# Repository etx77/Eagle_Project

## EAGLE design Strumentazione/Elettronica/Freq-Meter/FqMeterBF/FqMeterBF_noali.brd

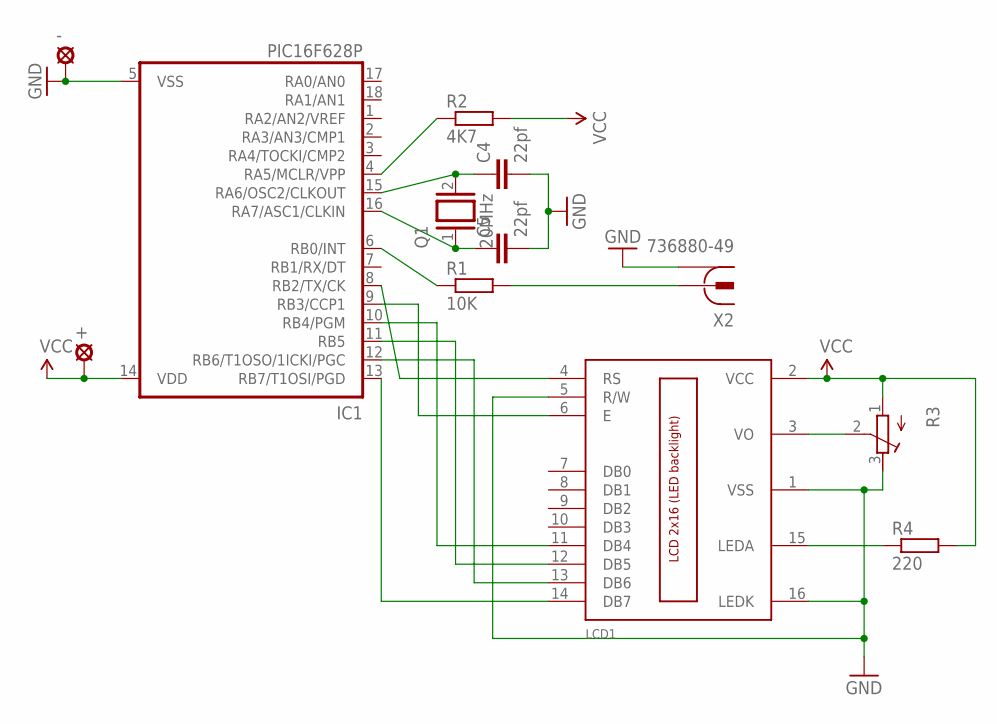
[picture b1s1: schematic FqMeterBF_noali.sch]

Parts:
+: LSP10
-: LSP10
C4, C5: 22pf; C025-024X044
IC1: PIC16F628P; DIL18
LCD1: LCD_2X16; HY-1602F
Q1: 20MHz; QS
R1: 10K; 0207/12
R2: 4K7; 0207/12
R3: R-TRIMM3339P; RTRIM3339P
R4: 220; 0207/12
X2: 736880-49

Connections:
GND: -.MP, C4.2, C5.2, IC1.5 (VSS), LCD1.1 (VSS), LCD1.5 (R/W), LCD1.16 (LEDK), R3.3 (E), X2.1, X2.1@1 (1), X2.1@2 (1)
unnamed: LCD1.15 (LEDA), R4.1
unnamed: C4.1, IC1.15 (RA6/OSC2/CLKOUT), Q1.2
unnamed: C5.1, IC1.16 (RA7/ASC1/CLKIN), Q1.1
unnamed: IC1.6 (RB0/INT), R1.1
unnamed: IC1.4 (RA5/MCLR/VPP), R2.1
unnamed: IC1.8 (RB2/TX/CK), LCD1.4 (RS)
unnamed: IC1.9 (RB3/CCP1), LCD1.6 (E)
unnamed: R1.2, X2.2
unnamed: LCD1.3 (VO), R3.2 (S)
unnamed: IC1.10 (RB4/PGM), LCD1.11 (DB4)
unnamed: IC1.11 (RB5), LCD1.12 (DB5)
unnamed: IC1.12 (RB6/T1OSO/1ICKI/PGC), LCD1.13 (DB6)
unnamed: IC1.13 (RB7/T1OSI/PGD), LCD1.14 (DB7)
unnamed: +.MP, IC1.14 (VDD), LCD1.2 (VCC), R2.2, R3.1 (A), R4.2

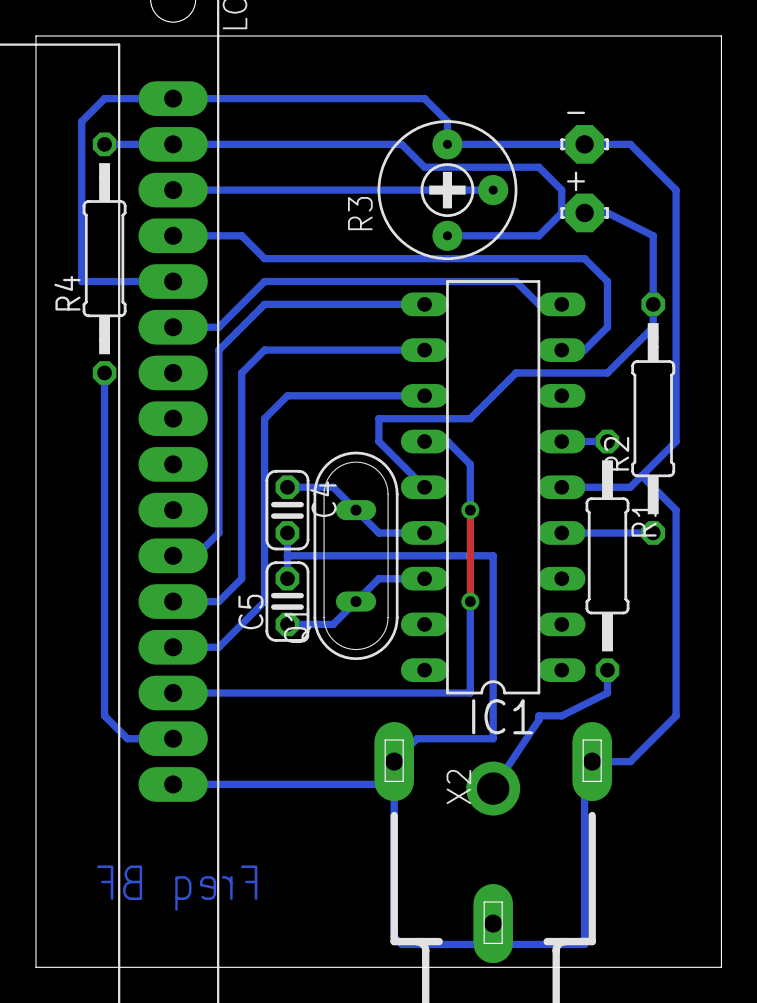
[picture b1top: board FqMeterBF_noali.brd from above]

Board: 2 copper layers, 38.1 x 51.7 mm, 12 parts (0 on the bottom side), 15 nets.

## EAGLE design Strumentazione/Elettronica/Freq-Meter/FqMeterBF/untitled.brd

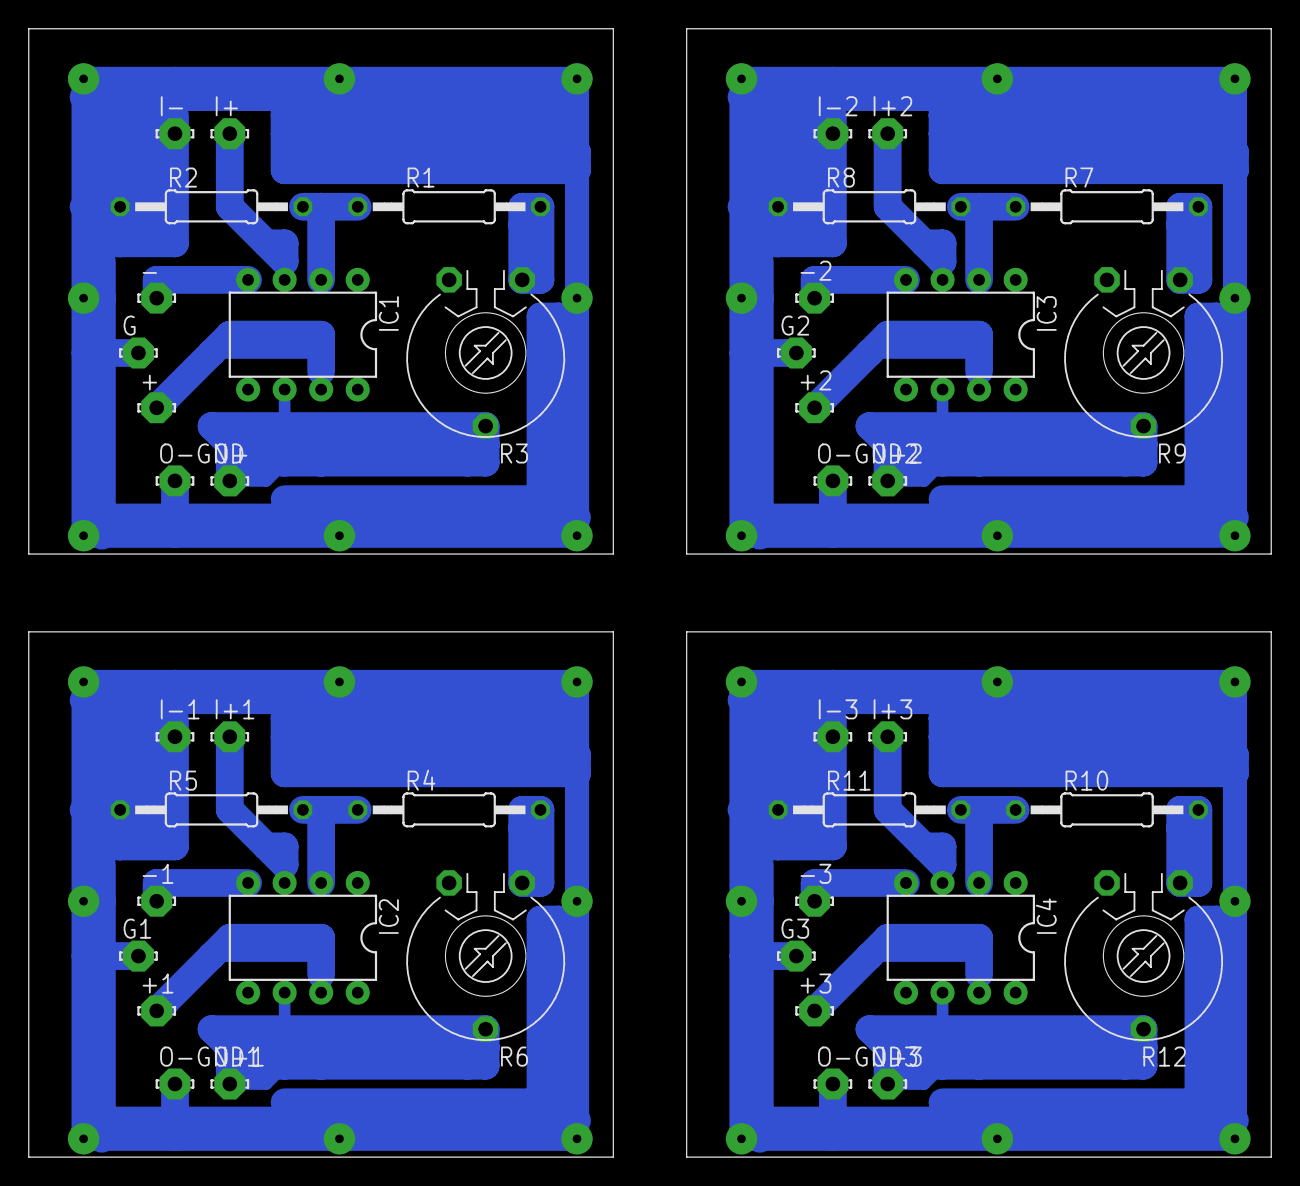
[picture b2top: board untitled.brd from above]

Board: 2 copper layers, 86.3 x 78.4 mm, 44 parts (0 on the bottom side), 28 nets.

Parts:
+, +1, +2, +3: LSP10
-, -1, -2, -3: LSP10
G, G1, G2, G3: LSP10
I+, I+1, I+2, I+3: LSP10
I-, I-1, I-2, I-3: LSP10
IC1, IC2, IC3, IC4: LM741P; DIL08
O+, O+1, O+2, O+3: LSP10
O-GND, O-GND1, O-GND2, O-GND3: LSP10
R1, R4, R7, R10: 68K; 0207/12
R2, R5, R8, R11: 1K2; 0207/12
R3, R6, R9, R12: 47K; PT-10

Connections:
+12V: +.MP, IC1.7
+12V1: +1.MP, IC2.7
+12V2: +2.MP, IC3.7
+12V3: +3.MP, IC4.7
-12V: -.MP, IC1.4
-12V1: -1.MP, IC2.4
-12V2: -2.MP, IC3.4
-12V3: -3.MP, IC4.4
unnamed: IC1.2, R1.1, R2.2
unnamed: R1.2, R3.1
unnamed: IC1.6, O+.MP, R3.3
unnamed: I+.MP, IC1.3
unnamed: G.MP, I-.MP, O-GND.MP, R2.1
unnamed: IC2.2, R4.1, R5.2
unnamed: R4.2, R6.1
unnamed: IC2.6, O+1.MP, R6.3
unnamed: I+1.MP, IC2.3
unnamed: G1.MP, I-1.MP, O-GND1.MP, R5.1
unnamed: IC3.2, R7.1, R8.2
unnamed: R7.2, R9.1
unnamed: IC3.6, O+2.MP, R9.3
unnamed: I+2.MP, IC3.3
unnamed: G2.MP, I-2.MP, O-GND2.MP, R8.1
unnamed: IC4.2, R10.1, R11.2
unnamed: R10.2, R12.1
unnamed: IC4.6, O+3.MP, R12.3
unnamed: I+3.MP, IC4.3
unnamed: G3.MP, I-3.MP, O-GND3.MP, R11.1

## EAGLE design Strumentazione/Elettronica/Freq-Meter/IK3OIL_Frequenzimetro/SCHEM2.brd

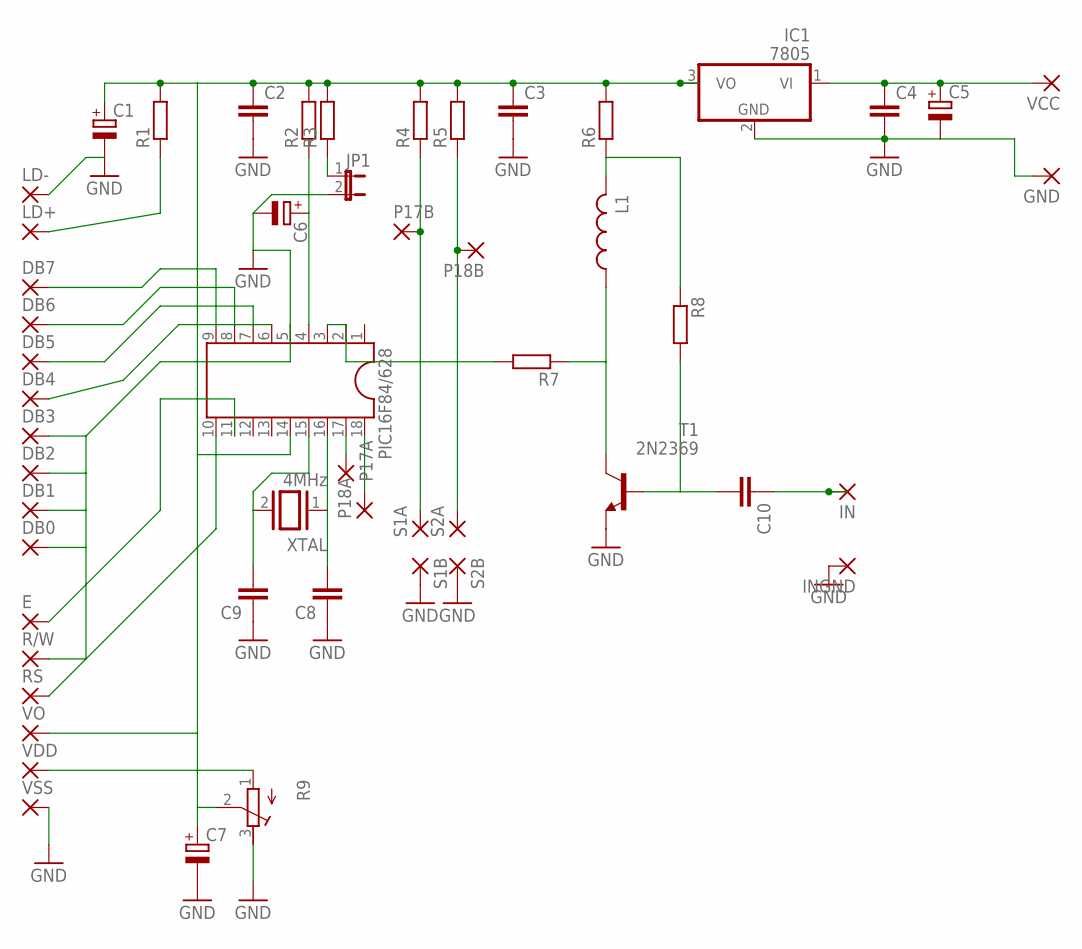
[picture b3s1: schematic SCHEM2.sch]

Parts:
C1, C5, C6, C7: CPOL-EUE3.5-8; E3,5-8
C2, C3, C4, C8, C9, C10: C-EU025-040X050; C025-040X050
DB0, DB1, DB2, DB3, DB4, DB5, DB6, DB7: WIREPAD1,6/0,8; 1,6/0,8
E: WIREPAD1,6/0,8; 1,6/0,8
GND: WIREPAD1,6/0,8; 1,6/0,8
IC1: 7805; TO220V
IN: WIREPAD1,6/0,8; 1,6/0,8
INGND: WIREPAD1,6/0,8; 1,6/0,8
JP1: JP1E; JP1
L1: L-US0204/7; 0204/7
LD+: WIREPAD1,6/0,8; 1,6/0,8
LD-: WIREPAD1,6/0,8; 1,6/0,8
P17A, P17B, P18A, P18B: WIREPAD1,6/0,8; 1,6/0,8
PIC16F84/628: DIL18
R1, R2, R3, R4, R5, R6, R7, R8: R-EU_0204/5; 0204/5
R9: R-TRIMM3339P; RTRIM3339P
R/W: WIREPAD1,6/0,8; 1,6/0,8
RS: WIREPAD1,6/0,8; 1,6/0,8
S1A, S1B, S2A, S2B: WIREPAD1,6/0,8; 1,6/0,8
T1: 2N2369; TO18
VCC: WIREPAD1,6/0,8; 1,6/0,8
VDD: WIREPAD1,6/0,8; 1,6/0,8
VO: WIREPAD1,6/0,8; 1,6/0,8
VSS: WIREPAD1,6/0,8; 1,6/0,8
XTAL: 4MHz; QS

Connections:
GND: C1.-, C2.2, C3.2, C4.2, C5.-, C6.-, C7.-, C8.1, C9.1, DB0.1, DB1.1, DB2.1, DB3.1, GND.1, IC1.2 (GND), INGND.1, JP1.2, LD-.1, PIC16F84/628.5, R9.3 (E), R/W.1, S1B.1, S2B.1, T1.1 (E), VSS.1
unnamed: C1.+, C2.1, C3.1, C7.+, IC1.3 (VO), PIC16F84/628.14, R1.2, R2.2, R3.2, R4.2, R5.2, R6.2, R9.2 (S), VO.1
unnamed: L1.2, R6.1, R8.1
unnamed: C4.1, C5.+, IC1.1 (VI), VCC.1
unnamed: JP1.1, R3.1
unnamed: L1.1, R7.1, T1.3 (C)
unnamed: C10.2, R8.2, T1.2 (B)
unnamed: C10.1, IN.1
unnamed: DB4.1, PIC16F84/628.6
unnamed: DB5.1, PIC16F84/628.7
unnamed: LD+.1, R1.1
unnamed: C6.+, PIC16F84/628.4, R2.1
unnamed: DB6.1, PIC16F84/628.8
unnamed: DB7.1, PIC16F84/628.9
unnamed: PIC16F84/628.2, PIC16F84/628.3, R7.2
unnamed: C9.2, PIC16F84/628.15, XTAL.2
unnamed: C8.2, PIC16F84/628.16, XTAL.1
unnamed: P18B.1, R5.1, S2A.1
unnamed: P17B.1, R4.1, S1A.1
unnamed: PIC16F84/628.10, RS.1
unnamed: P17A.1, PIC16F84/628.17
unnamed: P18A.1, PIC16F84/628.18
unnamed: R9.1 (A), VDD.1
unnamed: E.1, PIC16F84/628.11

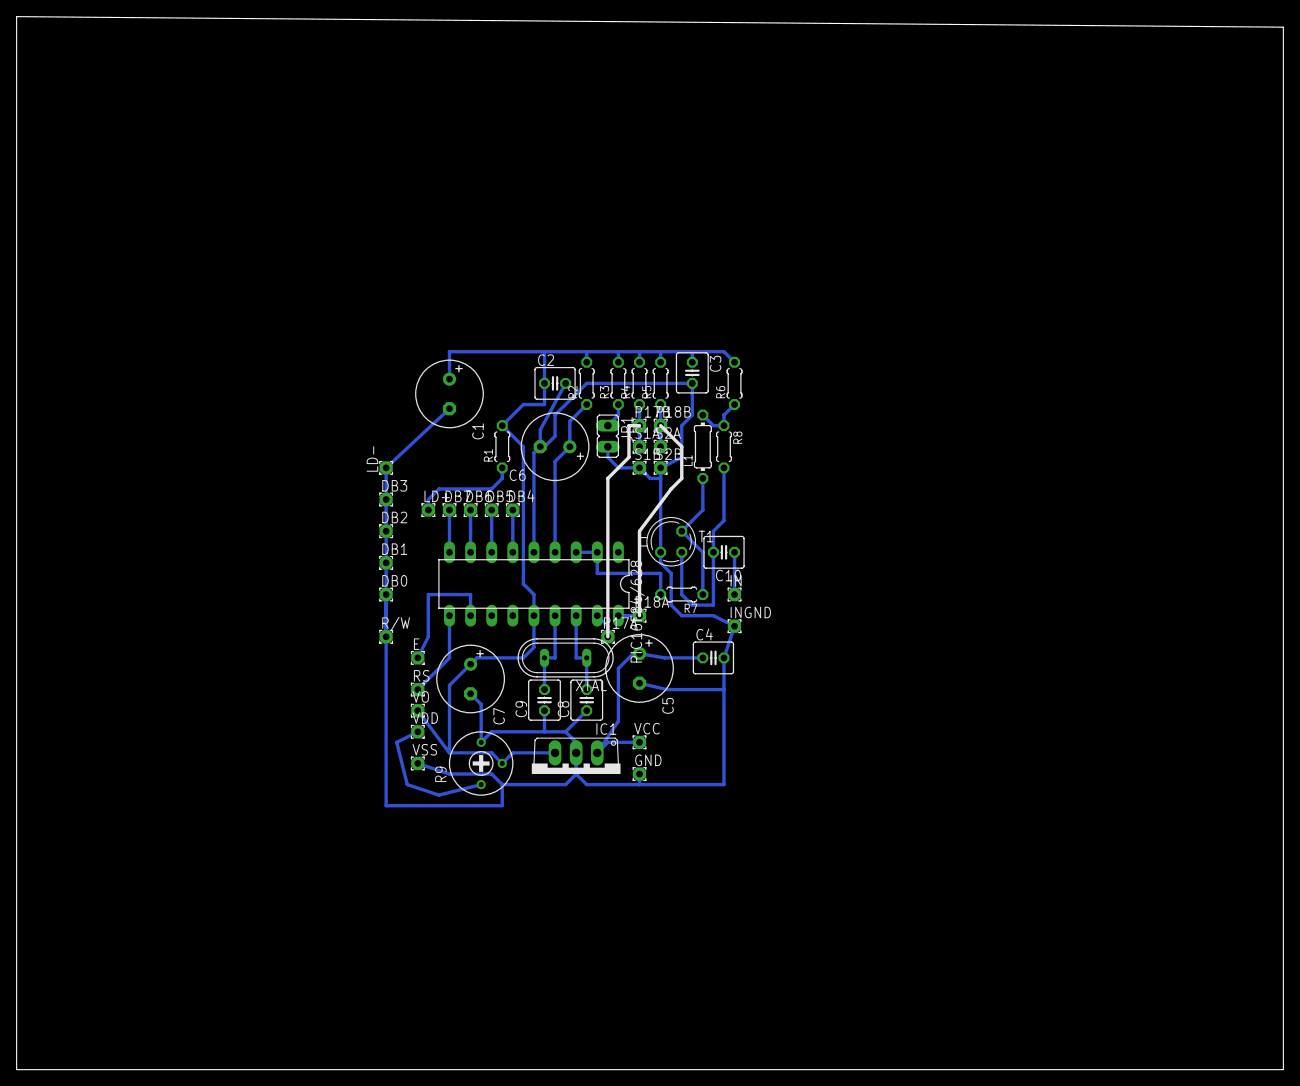
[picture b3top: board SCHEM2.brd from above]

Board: 2 copper layers, 152.4 x 126.7 mm, 53 parts (0 on the bottom side), 24 nets.

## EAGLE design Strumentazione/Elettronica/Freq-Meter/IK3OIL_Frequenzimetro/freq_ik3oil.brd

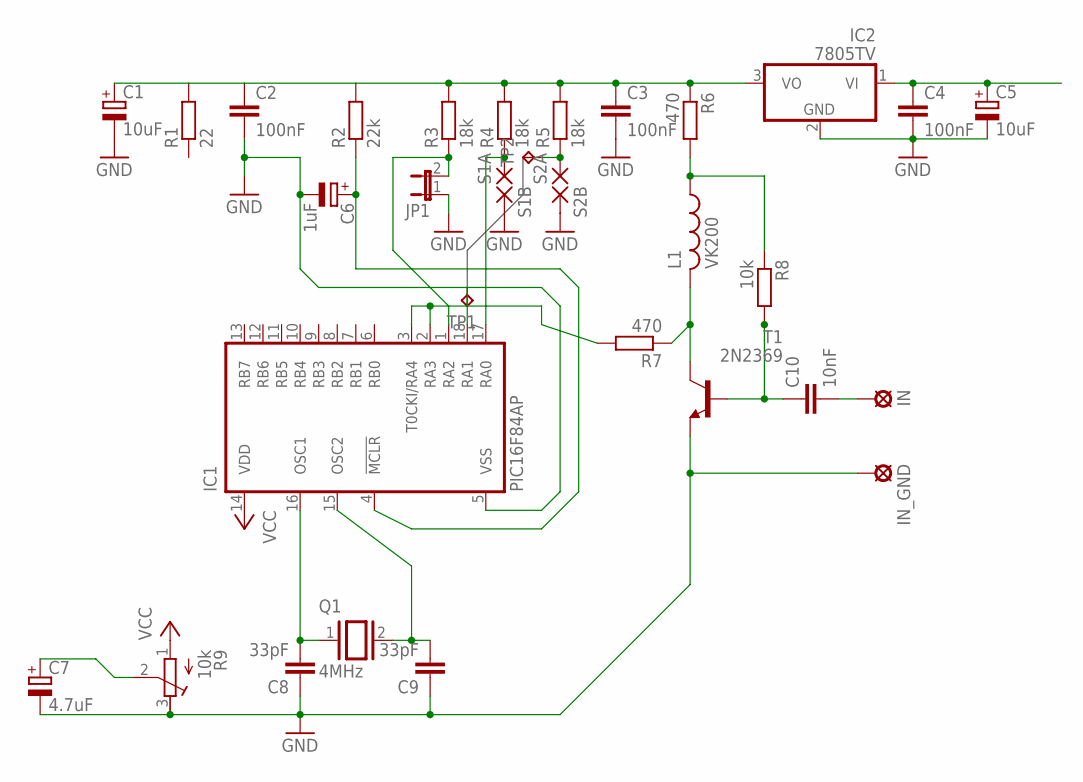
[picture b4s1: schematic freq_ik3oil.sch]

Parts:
C1, C5: 10uF; E2,5-7
C2, C3, C4: 100nF; C050-024X044
C6: 1uF; E2,5-7
C7: 4.7uF; E2,5-7
C8, C9: 33pF; C050-024X044
C10: 10nF; C050-024X044
IC1: PIC16F84AP; DIL18
IC2: 7805TV; TO220V
IN: LSP10
IN_GND: LSP10
JP1: JP1E; JP1
L1: VK200; TFI0307
Q1: 4MHz; QS
R1: 22; 0204/7
R2: 22k; 0204/7
R3, R4, R5: 18k; 0204/7
R6, R7: 470; 0204/7
R8: 10k; 0204/7
R9: 10k; RTRIM3339P
S1A, S1B, S2A, S2B: 1,6/0,8
T1: 2N2369; TO18
TP1, TP2: TPB1,27; B1,27

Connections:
GND: C1.-, C2.2, C3.2, C4.2, C5.-, C6.-, C7.-, C8.1, C9.1, IC1.5 (VSS), IC2.2 (GND), IN_GND.MP, JP1.1, R9.3 (E), S1B.1, S2B.1, T1.1 (E)
unnamed: C1.+, C2.1, C3.1, IC2.3 (VO), R1.2, R2.2, R3.2, R4.2, R5.2, R6.1
unnamed: C4.1, C5.+, IC2.1 (VI)
unnamed: IC1.1 (RA2), JP1.2, R3.1
unnamed: IC1.18 (RA1), TP1.TP
unnamed: C6.+, IC1.4 (!MCLR), R2.1
unnamed: C8.2, IC1.16 (OSC1), Q1.1
unnamed: C9.2, IC1.15 (OSC2), Q1.2
unnamed: IC1.17 (RA0), R4.1, S1A.1
unnamed: C10.1, R8.2, T1.2 (B)
unnamed: C10.2, IN.MP
unnamed: L1.2, R7.1, T1.3 (C)
unnamed: C7.+, R9.2 (S)
unnamed: L1.1, R6.2, R8.1
unnamed: R5.1, S2A.1, TP2.TP
unnamed: IC1.2 (RA3), IC1.3 (T0CKI/RA4), R7.2
VCC: IC1.14 (VDD), R9.1 (A)

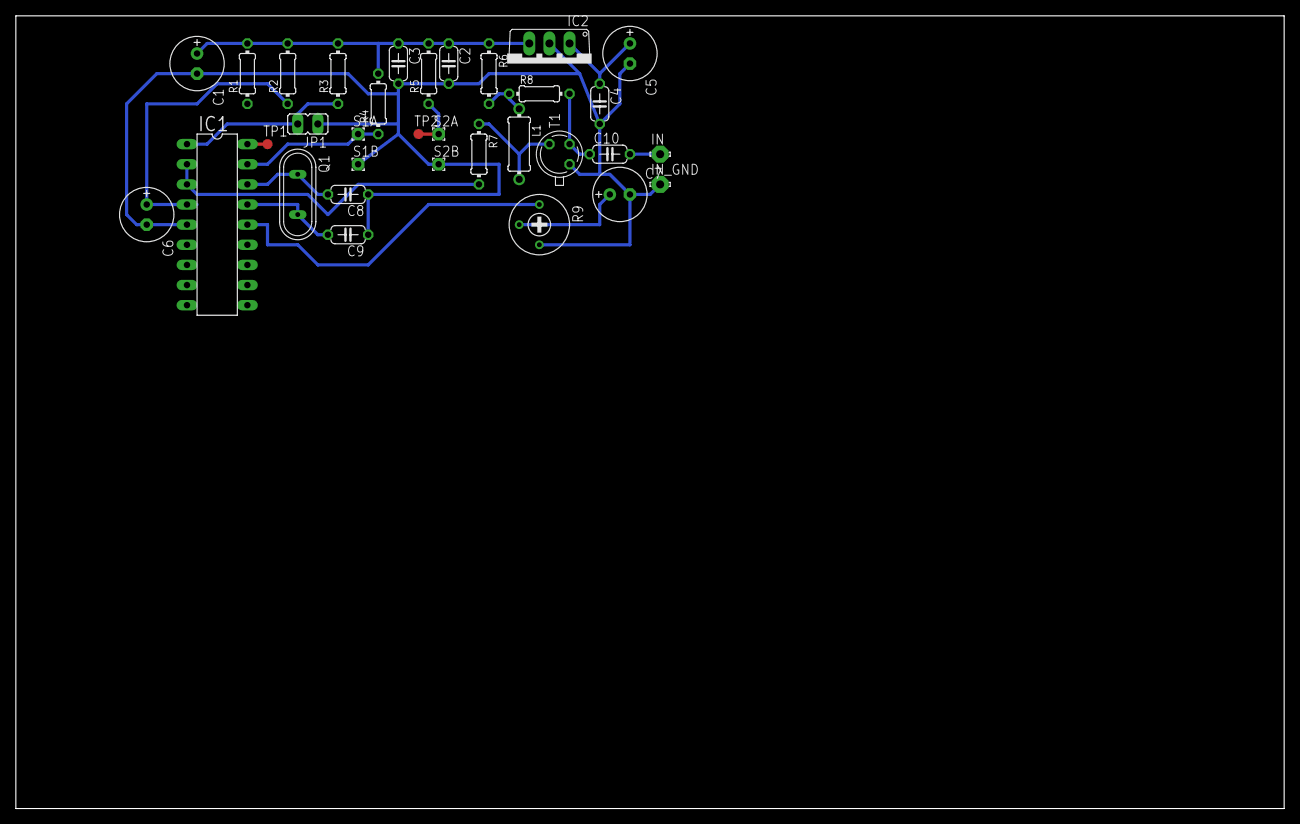
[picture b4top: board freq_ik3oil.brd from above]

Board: 2 copper layers, 160.0 x 100.0 mm, 33 parts (0 on the bottom side), 17 nets.

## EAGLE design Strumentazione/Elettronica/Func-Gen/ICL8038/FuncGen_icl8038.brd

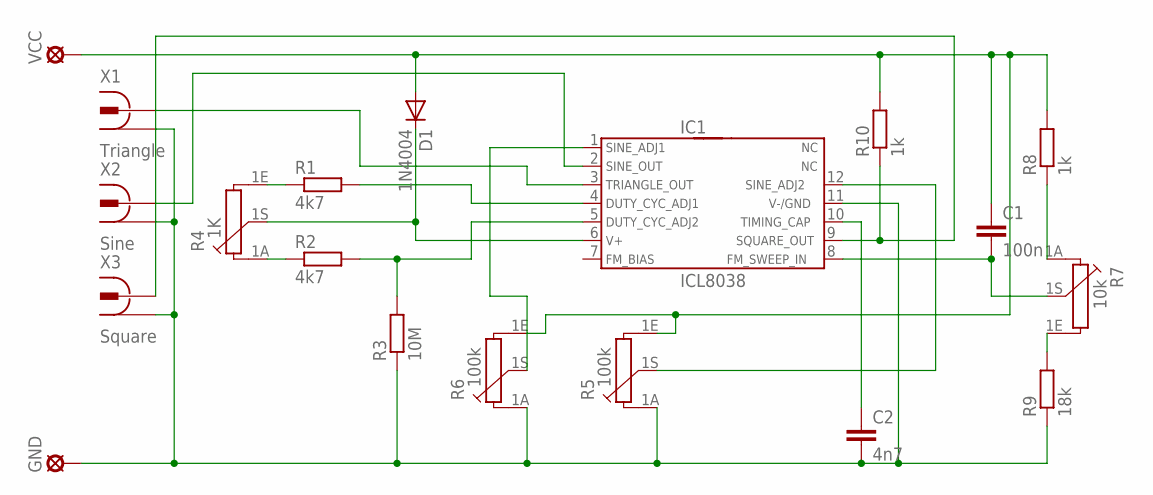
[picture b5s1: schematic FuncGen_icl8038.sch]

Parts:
C1: 100n; C025-025X050
C2: 4n7; C025-025X050
D1: 1N4004; DO41-10
GND: LSP10
IC1: ICL8038
R1, R2: 4k7; 0207/10
R3: 10M; 0207/10
R4: 1K; PC16S
R5, R6: 100k; PC16S
R7: 10k; PC16S
R8, R10: 1k; 0207/10
R9: 18k; 0207/10
VCC: LSP10
X1: Triangle; 736880-49
X2: Sine; 736880-49
X3: Square; 736880-49

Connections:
unnamed: C2.2, GND.MP, IC1.11, R3.1, R5.1A, R6.1A, R9.1, X1.1, X1.1@1 (1), X1.1@2 (1), X2.1, X2.1@1 (1), X2.1@2 (1), X3.1, X3.1@1 (1), X3.1@2 (1)
unnamed: R1.1, R4.1E
unnamed: R2.1, R4.1A
unnamed: D1.C, IC1.6, R4.1S
unnamed: IC1.4, R1.2
unnamed: IC1.5, R2.2, R3.2
unnamed: IC1.9, R10.1, X3.2
unnamed: C1.1, D1.A, R5.1E, R6.1E, R8.2, R10.2, VCC.MP
unnamed: IC1.1, R6.1S
unnamed: IC1.12, R5.1S
unnamed: C2.1, IC1.10
unnamed: R7.1E, R9.2
unnamed: R7.1A, R8.1
unnamed: C1.2, IC1.8, R7.1S
unnamed: IC1.3, X1.2
unnamed: IC1.2, X2.2

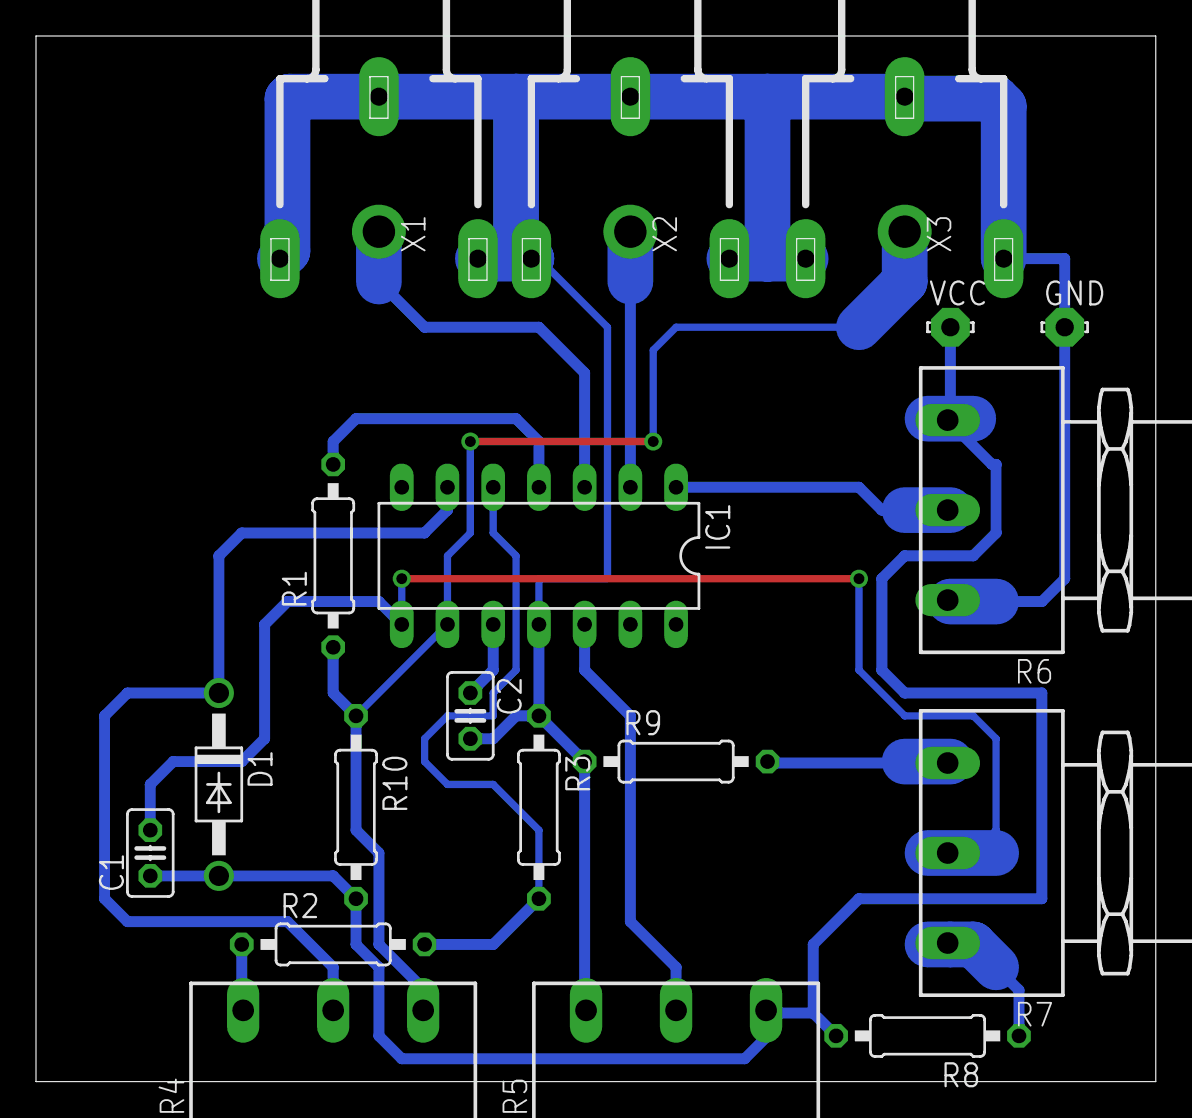
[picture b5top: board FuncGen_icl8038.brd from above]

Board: 2 copper layers, 62.2 x 58.1 mm, 19 parts (0 on the bottom side), 16 nets.

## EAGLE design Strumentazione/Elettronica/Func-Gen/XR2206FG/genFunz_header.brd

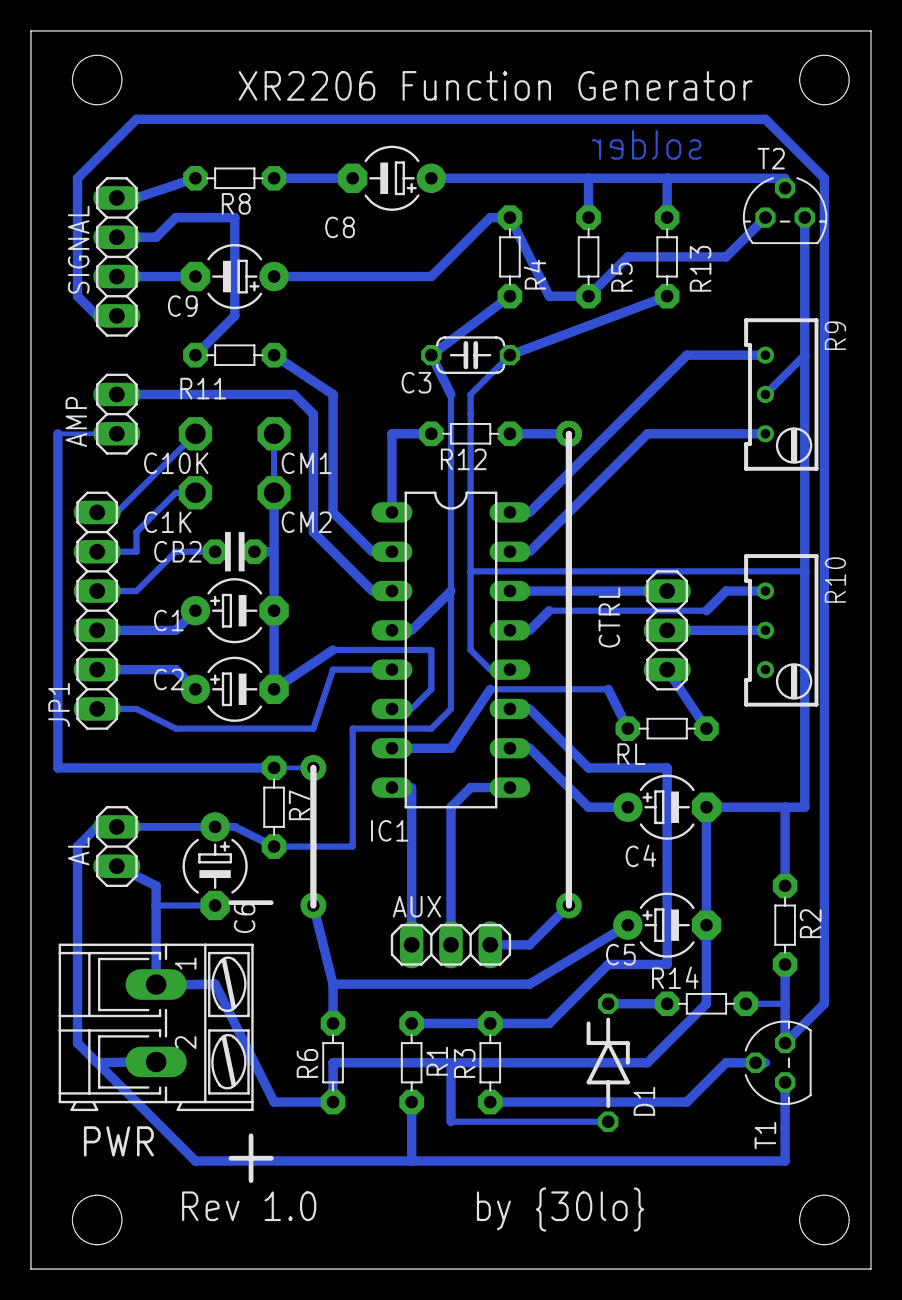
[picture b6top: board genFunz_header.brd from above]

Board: 2 copper layers, 54.3 x 80.0 mm, 39 parts (0 on the bottom side), 34 nets.

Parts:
AL: 1X02
AMP: 1X02
AUX: 1X03
C1, C4: 1uF; E5-4
C1K, C10K: TPPAD1-13; P1-13
C2, C5: 10uF; E5-4
C3: 100nF; C050-024X044
C6: 2.2uF; E5-4
C8, C9: 100uF; E5-4
CB2: 100nF; C-2,5
CM1, CM2: TPPAD1-13; P1-13
CTRL: 1X03
D1: 4.7V; ZDIO-7.5
IC1: XR2206; DIL16
JP1: 1X06
PWR: AK300/2
R1: 5.6K; R-5
R2: 1K; R-5
R3, R8: 10K; R-5
R4: 4.7K; R-5
R5: 39K; R-5
R6: 3.3k; R-5
R7: 3,3K; R-5
R9, R10: 500; RTRIM64W
R11: 220; R-5
R12, R14: 100; R-5
R13: 47K; R-5
RL: 2.2K; R-5
SIGNAL: 1X04
T1, T2: BC547; TO92

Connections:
GND: AL.1, C3.2, C4.-, C5.-, C6.-, D1.A, IC1.12, PWR.1, R2.1, R6.1, R9.2, R13.1, T2.1
unnamed: IC1.15, R9.3
unnamed: IC1.16, R9.1
unnamed: IC1.13, R10.1
unnamed: AMP.2, C5.+, R6.2, R7.1
unnamed: C8.-, R8.1
unnamed: IC1.11, R1.1, R3.2
unnamed: AMP.1, IC1.3
unnamed: IC1.7, RL.2
unnamed: C1.-, C2.-, CB2.1, CM1.1, CM2.1, IC1.6
unnamed: C4.+, IC1.10
unnamed: C8.+, R5.2, R13.2, T2.2
unnamed: R3.1, T1.2
unnamed: C9.-, SIGNAL.2
unnamed: C1K.1, JP1.5
unnamed: CTRL.2, R10.2
unnamed: CTRL.3, IC1.14
unnamed: IC1.2, R11.2
unnamed: CTRL.1, RL.1
unnamed: C1.+, JP1.3
unnamed: R11.1, SIGNAL.3
unnamed: AUX.3, R12.1
unnamed: AUX.1, IC1.8
unnamed: AUX.2, IC1.9
unnamed: IC1.1, R12.2
unnamed: CB2.2, JP1.4
unnamed: C2.+, JP1.2
unnamed: R8.2, SIGNAL.4
unnamed: C10K.1, JP1.6
unnamed: D1.C, R14.1
unnamed: IC1.5, JP1.1
unnamed: R2.2, R14.2, SIGNAL.1, T1.1
unnamed: C9.+, R4.1, R5.1, T2.3
VCC: AL.2, C3.1, C6.+, IC1.4, PWR.2, R1.2, R4.2, R7.2, T1.3

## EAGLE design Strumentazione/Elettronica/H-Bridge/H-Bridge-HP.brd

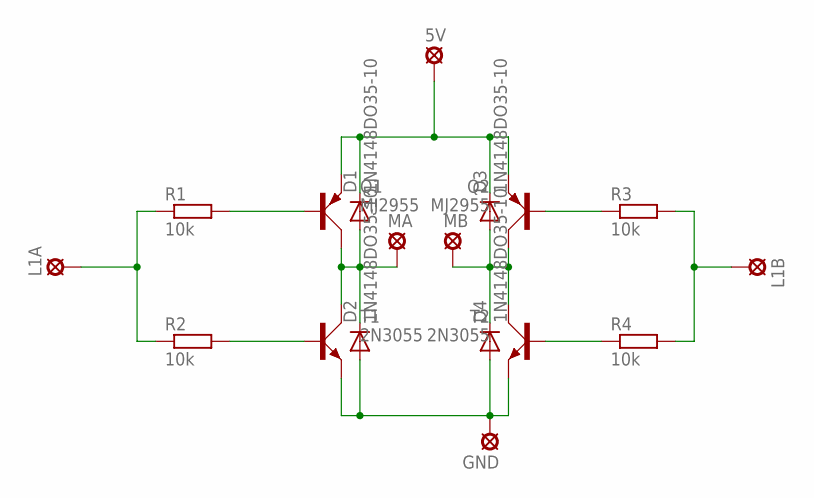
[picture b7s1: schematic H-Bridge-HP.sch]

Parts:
5V: LSP10
D1, D2, D3, D4: 1N4148DO35-10; DO35-10
GND: LSP10
L1A, L1B: LSP10
MA: LSP10
MB: LSP10
Q1, Q2: MJ2955; TO3A
R1, R2, R3, R4: 10k; 0309/12
T1, T2: 2N3055; TO3A

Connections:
unnamed: L1A.MP, R1.1, R2.1
unnamed: Q1.B, R1.2
unnamed: R2.2, T1.B
unnamed: D1.A, D2.C, MA.MP, Q1.C, Q1.C1 (C), T1.C, T1.C1 (C)
unnamed: D3.A, D4.C, MB.MP, Q2.C, Q2.C1 (C), T2.C, T2.C1 (C)
unnamed: Q2.B, R3.1
unnamed: R4.1, T2.B
unnamed: L1B.MP, R3.2, R4.2
unnamed: D2.A, D4.A, GND.MP, T1.E, T2.E
unnamed: 5V.MP, D1.C, D3.C, Q1.E, Q2.E

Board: 2 copper layers, 18 parts (0 on the bottom side), 10 nets, no tracks yet.

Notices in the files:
parts and their libraries:
SparkFun-Aesthetics: Licensing: Creative Commons ShareAlike 4.0 International - https://creativecommons.org/licenses/by-sa/4.0
